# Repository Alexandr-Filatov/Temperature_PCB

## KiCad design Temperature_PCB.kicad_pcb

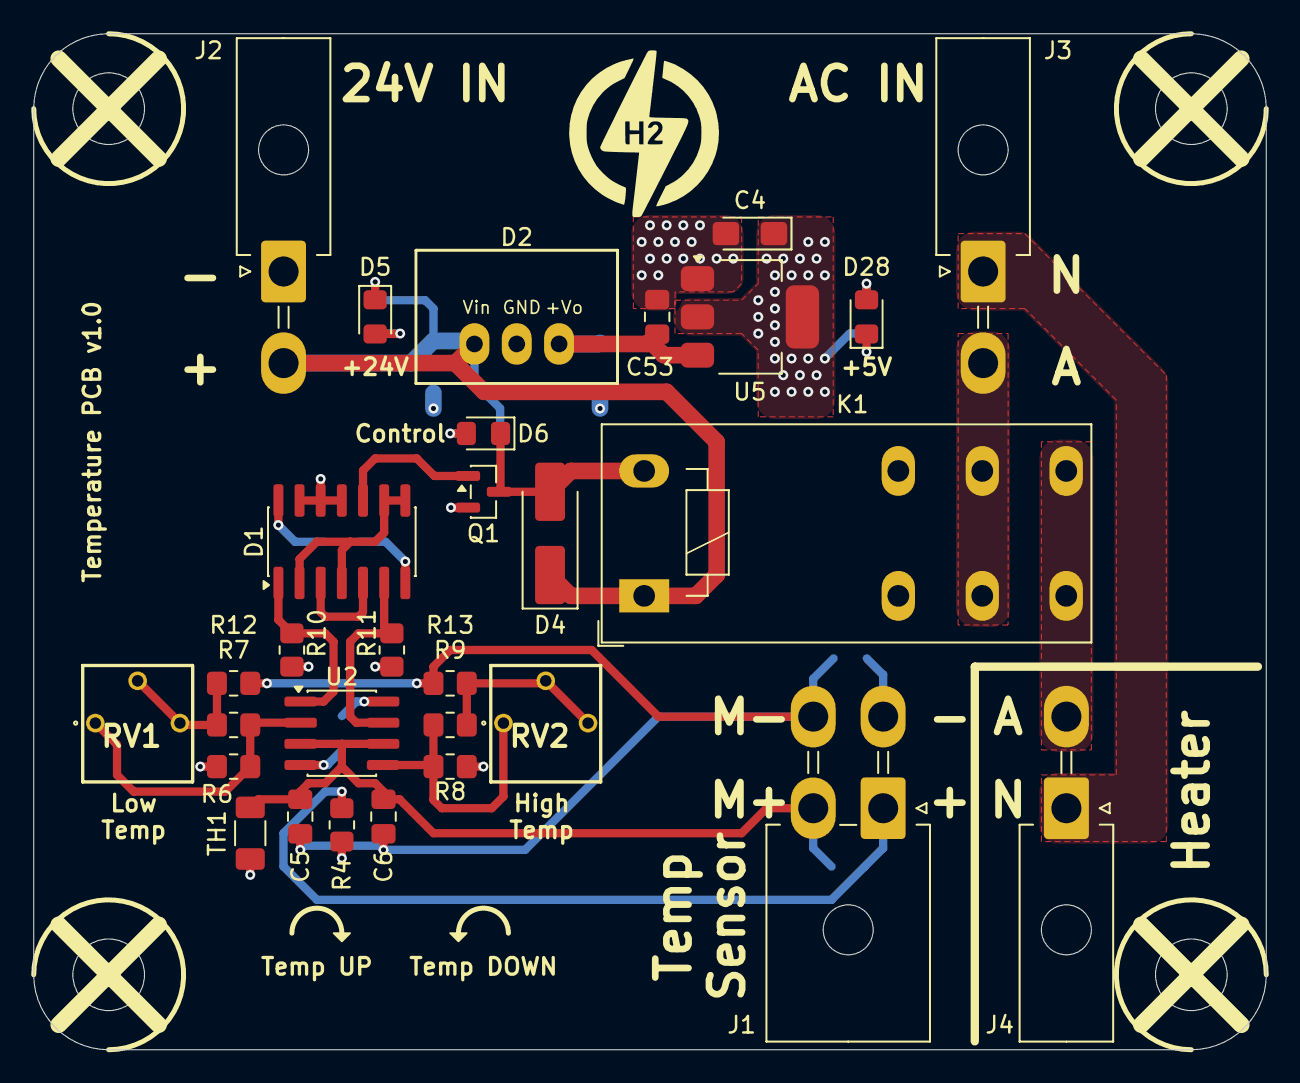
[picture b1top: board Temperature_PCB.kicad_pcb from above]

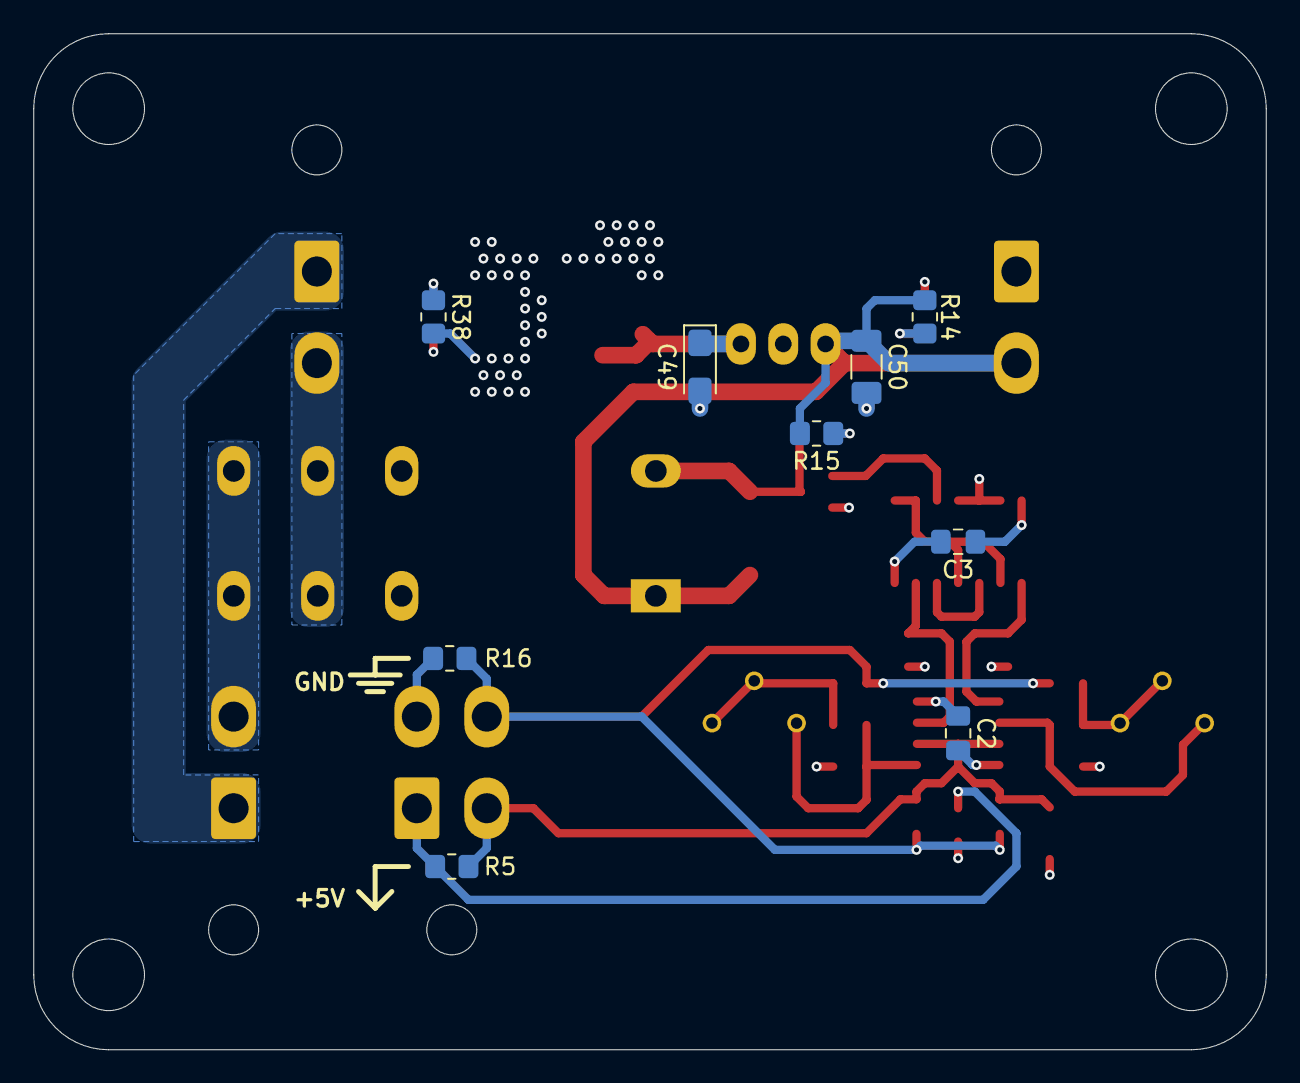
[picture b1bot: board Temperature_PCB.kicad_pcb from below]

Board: 4 copper layers, 74.0 x 61.0 mm, 44 parts (9 on the bottom side), 23 nets.

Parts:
C2, C3, C5, C6, C53: 100n; C_0805_2012Metric_Pad1.18x1.45mm_HandSolder
C4: 22u; CP_EIA-3216-18_Kemet-A_HandSolder
C49: 10u; CP_EIA-3216-18_Kemet-A_HandSolder
C50: 10u; C_1206_3216Metric_Pad1.33x1.80mm_HandSolder
D1: SO-14_3.9x8.65mm_P1.27mm
D2: K78xx-500R3
D3: Logo; Logo_Company_2
D4: D_SMA_Handsoldering
D5, D6, D28: LED_0805_2012Metric_Pad1.15x1.40mm_HandSolder
H1, H2, H3, H4: MountingHole; MountingHole_4.3mm_M4
J1: Molex_Mini-Fit_Jr_5569-04A2_2x02_P4.20mm_Horizontal
J2, J3, J4: Molex_Mini-Fit_Jr_5569-02A2_2x01_P4.20mm_Horizontal
K1: Relay_DPDT_Schrack-RT2-FormC_RM5mm
Q1: SOT-23
R4, R6, R8: 2.2k; R_0805_2012Metric_Pad1.20x1.40mm_HandSolder
R5, R16: 0; R_0805_2012Metric_Pad1.20x1.40mm_HandSolder
R7: 49.9; R_0805_2012Metric_Pad1.20x1.40mm_HandSolder
R9: 330; R_0805_2012Metric_Pad1.20x1.40mm_HandSolder
R10, R11: 10k; R_0805_2012Metric_Pad1.20x1.40mm_HandSolder
R12, R13, R38: 1k; R_0805_2012Metric_Pad1.20x1.40mm_HandSolder
R14, R15: 3k; R_0805_2012Metric_Pad1.20x1.40mm_HandSolder
RV1, RV2: 3362P_1
TH1: Thermistor_NTC; R_1206_3216Metric_Pad1.30x1.75mm_HandSolder
U2: SOIC-8_3.9x4.9mm_P1.27mm
U5: SOT-223-3_TabPin2

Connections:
+5V: C2.1, C3.1, C4.1, D1.14 (Vdd), R4.2, R6.2, R8.2, R10.2, R11.2, R38.2, U2.8 (V+), U5.2 (VO)
+24V: C50.1, D2.1 (Vin), D4.1 (K), J2.2, K1.A1, R14.2, R15.2
/+9V: C49.1, C53.1, D2.3 (+Vo), U5.3 (VI)
/A_IN: J3.2, K1.11, K1.21
/A_OUT: J4.2, K1.14, K1.24
/Control: D1.10 (~EF), Q1.1 (G)
/N: J3.1, J4.1
GND: C2.2, C3.2, C4.2, C49.2, C50.2, C53.2, D1.7 (Vss), D1.11 (~HG), D1.12 (G), D1.13 (H), D2.2 (GND), D5.1 (K), D28.1 (K), J1.3, J2.1, Q1.2 (S), R16.1, TH1.2, U2.4 (V-), U5.1 (GND)
unnamed: D1.1 (A), R10.1, U2.1
unnamed: D1.2 (B), D1.4 (~CD), D1.8 (E), D1.9 (F)
unnamed: D1.3 (~AB), D1.5 (C)
unnamed: D1.6 (D), R11.1, U2.7
unnamed: D4.2 (A), D6.1 (K), K1.A2, Q1.3 (D)
unnamed: D5.2 (A), R14.1
unnamed: D6.2 (A), R15.1
unnamed: D28.2 (A), R38.1
unnamed: J1.1, R4.1, R5.2
unnamed: C5.2, C6.2, J1.2, R5.1, TH1.1, U2.3 (+), U2.6 (-)
unnamed: C5.1, C6.1, J1.4, R12.1, R13.1, R16.2
unnamed: R7.1, R12.2, RV1.2, RV1.3
unnamed: R9.1, R13.2, RV2.2, RV2.3
unnamed: R6.1, R7.2, RV1.1, U2.2 (-)
unnamed: R8.1, R9.2, RV2.1, U2.5 (+)

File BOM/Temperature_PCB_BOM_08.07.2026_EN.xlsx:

Reference | Value | Product Name | Replacement | Package | Description | Quantity | DNP
C2, C3, C5, C6, C53 | 100n |  |  | SMD 0805 | Capacitor SMD 50V | 5
C49 | 10u | CA45-A010K106T |  | CP EIA-3216-18 Kemet-A | Capacitor Tantalum SMD 10V | 1
C50 | 10u |  |  | SMD 1206 | Capacitor SMD 50V | 1
C4 | 22u | CA45-A010K226T |  | CP EIA-3216-18 Kemet-A | Capacitor Tantalum SMD 10V | 1
D2 | ~ | K7809-500R3 |  | K78xx-500R3 | DCDC | 1
D4 | ~ | 1N4007[M7] |  | SMA | Diode | 1
D5, D6, D28 | ~ | FYLS-0805UYC |  | SMD 0805 | Yellow LED | 3
D1 | ~ | CD4011 |  | SO-14 3.9x8.65mm P1.27mm | NAND | 1
J2, J3, J4 | ~ | DS1073-01-2x1MR2T6 |  | Molex Mini-Fit Jr 5569-02A2 2x01 P4.20mm | Connector | 3
J1 | ~ | DS1073-01-2x2MR3T6 |  | Molex Mini-Fit Jr 5569-04A2 2x02 P4.20mm | Connector | 1
K1 | ~ | HF115F/024-1H3B |  | Relay DPDT Schrack-RT2-FormC RM5mm | Relay | 1
Q1 | ~ | 2N7002 |  | SOT-23 | MOSFET | 1
R5, R16 | 0 |  |  | SMD 0805 | Resistor SMD 1% | 2 | ✓
R10, R11 | 10k |  |  | SMD 0805 | Resistor SMD 1% | 2
R12, R13 | 1k | RT0805BRD0751RL |  | SMD 0805 | Resistor SMD 0.1% | 2
R38 | 1k |  |  | SMD 0805 | Resistor SMD 1% | 1
R4, R6, R8 | 2.2k |  |  | SMD 0805 | Resistor SMD 1% | 3
R9 | 330 | ERA6AEB331V |  | SMD 0805 | Resistor SMD 0.1% | 1
R14, R15 | 3k | Resistor SMD |  | SMD 0805 | Resistor SMD 1% | 2
R7 | 49.9 | RT0805BRD0749R9L |  | SMD 0805 | Resistor SMD 0.1% | 1
RV1, RV2 | ~ | JBR-3362P-102-R |  | 3362P 1 | Potentiometer | 2
U2 | ~ | LM393 |  | SOIC-8 3.9x4.9mm P1.27mm | Op-Amp | 1
U5 | ~ | AMS1117-5.0 |  | SOT-223-3 | Linear regulator | 1

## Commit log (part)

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2026-05-28 zero commit
2026-06-11 VER1.0: плата разведена, файлы для производства готовы
